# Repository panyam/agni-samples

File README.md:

# agni-samples

Real, publicly-licensed electronic designs that [agni](https://github.com/panyam/agni) reads in its
tests, its tutorial, and its reader cross-checks.

None of these designs are ours.  Someone else published each one under an open licence.  Each
folder keeps the upstream `LICENSE` that came with the design, and the KiCad boards under `boards/`
keep their upstream `README.md` too.  `PROVENANCE.md` records where each design came from, and what
was changed, if anything.

They live in their own repo, so the engine repo keeps a single licence and these keep theirs.

## The boards

| board | components | sheets | licence |
|---|---:|---:|---|
| `jetson-agx-thor-baseboard` | 1123 | 17 | Apache-2.0 |
| `royalblue54L-feather` | 71 | 1 | CERN-OHL-P |
| `hackrf-one` | 418 | 4 | CERN-OHL-P |
| `glasgow-revC3` | 257 | 3 | 0BSD |
| `cynthion` | 348 | 17 | CERN-OHL-P |
| `mnt-reform-motherboard30` | 529 | 13 | CERN-OHL-S |

ODB++ jobs sit apart, under `odb/` (see `PROVENANCE.md`).  Altium Designer wrote foxBMS's five
boards (CC-BY-4.0).  Allegro's tools wrote three more boards (CERN-OHL-S, CC-BY-4.0, OCP permissive).
kicad-cli exported each KiCad board above.

`cadence/` holds Cadence's other exports, and each has a `design.yaml`.  Allegro wrote the Parallella
parasdr to IPC-2581 and ODB++X (CC BY-SA 3.0 US), and its Allegro 16.6 board sits beside them.
OrCAD Capture wrote Clay R6 to EDIF (MIT).  Clay R6's Allegro 16.6 board sits beside it with
`pstxnet.dat`, the netlist Capture handed Allegro for that board.

`allegro/` holds Allegro boards, each as its publisher released it.  Four come from BeagleBoard.org
(CC-BY-4.0).  The BeagleBone AI comes with an extract that Allegro wrote from it.  BeaglePlay,
BeagleV-Fire and BeagleBone AI-64 come with other files Allegro wrote beside each board, such as
Gerbers and drill files, or a placement report.  BeagleBoard's Allegro boards use three `.brd`
header families, and these four cover all three.  The other two `.brd` boards are pc069 and the
OpenCellular breakout.  Each publisher also released an ODB++ job of the same board, under
`odb/allegro/`.  SLUGS v2 (MIT, Allegro 16.0), Parallella-I (CC BY-SA 3.0 US, 16.4) and the
ADALM1000 (CC BY-SA 3.0, 16.5) come from earlier releases, each with the netlist, films or exports
its publisher released beside it.

`altium/` holds Altium boards as Altium saved them.  The five foxBMS boards are binary `.PcbDoc`
files.  Two OpenSpeechPlatform boards (BSD-2-Clause) come as a binary `.PcbDoc` and the ASCII
`.PcbDoc` Altium saved of the same board, with their Gerbers.

`revisions/` holds later revisions of a board above, so two real revisions of one design can be
compared.  Antmicro's Jetson baseboard revs 1.1.2 and 1.1.3 sit there beside rev 1.1.0 in `boards/`
(Apache-2.0).  Rev 1.1.3 was saved by KiCad 10.  It ships in its own `revisions` tarball, so the oracle corpus the engine fetches on
every CI run stays the same size.  `make diff A=mount://boards/jetson-agx-thor-baseboard
B=mount://revisions/jetson-agx-thor-baseboard-1.1.2` compares the two.

`remote/` holds boards this repo may not redistribute, because their repos state no licence.  Only
`remote/remote.pin` is committed.  It names each file by its URL at a fixed commit and its sha256.
`make remote` downloads them from their publishers into a cache in `~/.cache/agni/samples`, so each
is downloaded once per machine, and copies them into `remote/<board>/`.  Three BeagleBoard.org
boards come this way: the BeagleBoard-X15 (Allegro 16.6), and the BeagleBone rev C2 and BeagleBone
Black rev B4 (16.4).  `make remote-clean` lists cache files unused for 30 days, and deletes them only
when you answer y.

## Opening them in agni

`agni serve` can open a checkout as it stands.  `agni.yaml` at the root mounts `boards/`, `odb/`,
`cadence/`, `allegro/`, `altium/`, `remote/` and `house/`, so `agni check mount://boards/hackrf-one` works at the
root with no flags.
Run it from the root.  agni finds `agni.yaml` from a subfolder too, but then reads its paths against
the folder you're in.  You need agni v0.6.0 or later, the first release that reads OrCAD Capture
designs, which Clay R6 is read from.  CI reads every design with v0.6.0 and with the latest release,
v0.6.2.  agni opens the seven binary `.PcbDoc` boards and five of the eleven Allegro `.brd` boards,
counting the two under `cadence/`.  BeaglePlay (Allegro 17.4), BeagleV-Fire (17.5), pc069, SLUGS v2,
Parallella-I and the ADALM1000 were saved by releases agni does not read yet (agni issue 1355), and
agni does not read an ASCII `.PcbDoc` yet (agni issue 1393).

```bash
make remote       # fetch the remote/ boards first, if you want them in the viewer
make serve        # the viewer over every board, job, native board and house board, at http://127.0.0.1:8080/
make serve-wasm   # the same, with each design analysed in your browser
make site         # the whole set as static files in site/, the way agni's public demo is built
```

`AGNI` names the binary and defaults to the `agni` on your PATH.  A release binary carries the
viewer.  A dev build (`make agni` in an agni checkout) carries none, so name its `web/` too:
`make serve AGNI=../agni/bin/agni WEB_DIR=../agni/web`.  `make site` and `make serve-wasm` need the
wasm engine built there as well (`make ui wasm`).  `PORT` moves the server, and `MCP=1` also serves
agni's analysis to an agent at `/mcp`.

`serve-wasm` caps a design at serve's `--wasm-max-bytes` (128 MB).  A bigger one goes to the server
engine, and the page says so.  Jetson is about 92 MB, so every board here runs in the browser.

`make verify` checks that each board folder has a `design.yaml` and a `PROVENANCE.md` section, and
that no `project.yaml` sits over the boards.  It also checks that each folder under `allegro/`,
`odb/allegro/` and `cadence/` has a `LICENSE` and a `PROVENANCE.md` heading, and that each design
under `cadence/` has a `design.yaml`.  `make verify AGNI=agni` also reads every design, job and house
board, and fails on any that reads as no components.  `make test` checks those checks, and CI runs
both.

## Your own boards beside these

A team can clone this repo and run every analysis on its own boards, after seeing each one work on a
public board first.  `make tour` runs every target below on Glasgow.

Your boards go in their own mount, `house`.  It defaults to `house/` in the checkout, and
`HOUSE_DIR=<folder>` moves it.  A folder outside the checkout is safer, since this repo is public.
`house/README.md` walks through adding a board from the template, with a `project.yaml` for your
team's conventions, checklists and query sets.  `make setup` installs a pre-commit hook that refuses
a commit with a house board in it.

Each target runs one agni command over `DESIGN=mount://...`.  `DESIGN` defaults to Glasgow.

| target | runs |
|---|---|
| `make check` | every rule, as text, and the verdict report in `reports/<name>-check.html` |
| `make review CHECKLIST=...` | a checklist walk, and its report in `reports/`.  Defaults to `examples/checklist.yaml` |
| `make diff A=... B=...` | the structural diff of two revisions or two views.  `RENAME_APPROX=1` pairs renamed nets that also changed |
| `make query SET=...` | a query set.  Defaults to `examples/queries.yaml` |
| `make trace FROM=U1.51 TO=U14.3` | the series path between two pins |
| `make lexicon` | the vocabulary agni uses to read the design's names |
| `make pinmap` | a row for each pin in the design's `io_map`, in `reports/<name>-pins.csv` |
| `make intake` | the sanitized summary, with no net name in it |
| `make trial` | the `agni trial` report, with no name from the design in it |

`reports/` is gitignored.  Every report in it carries your net names and reference designators,
except the intake and trial reports.  `DESIGN` and the other variables in the table take a value
from the make command line only.  So if your shell exports `DESIGN` for another project's Makefile,
these targets don't see it.

## Using these from the engine

The engine fetches a **pinned release tarball**, verified by checksum, into a gitignored directory.
It does not use a git submodule, so an engine clone does not carry this repo.

Tarballs are built per purpose, so a job downloads only what it needs:

| tarball | contents |
|---|---|
| `tutorial-board` | the Jetson baseboard, schematics only |
| `oracle-corpus` | every board, schematics and board files |
| `odb-altium` | ODB++ jobs Altium Designer wrote (the foxBMS boards), byte-identical to their publisher's |
| `altium` | the same foxBMS boards as Altium saved them (`.PcbDoc`), each held to its ODB++ export in `odb-altium`, and two OpenSpeechPlatform boards saved both as binary and as ASCII `.PcbDoc` |
| `odb-kicad` | each board above exported to ODB++ by kicad-cli, for reading a board both ways |
| `allegro` | the BeagleBone AI's Allegro `.brd`, with the extract Allegro wrote from the same board |
| `cadence-exports` | ODB++ jobs Allegro's tools wrote (`odb/allegro/`), and the IPC-2581 and EDIF exports under `cadence/` |
| `remote-boards` | `remote/remote.pin` alone, from which the engine fetches the `remote/` boards from their publishers |
| `revisions` | later revisions of the boards above, both views each, for comparing two revisions.  Only a demo or a revision example fetches it |
| `allegro-boards` | nine more Allegro `.brd` boards: six with the Gerbers, drill files, netlists, placement reports and OrCAD schematics their publishers released beside them, and three whose export is in `cadence-exports` |

`make dist` builds them all and writes `SHA256SUMS`.  `make list` prints the lines to pin.  `make
verify-dist` checks a built set against its sums.

Released artifacts are the pinned ones.  Verify a download against the `SHA256SUMS` attached to the
release rather than against a local rebuild, since archive metadata varies between machines.

## Adding a board

1. **Check the licence, and stop if there is not one.**  A design shipped with no LICENSE file cannot
   be redistributed here whatever its origin.  Permissive and reciprocal open-hardware licences are
   fine (PROVENANCE.md, "Reciprocal licences").  NonCommercial terms are not.
2. Copy the design **verbatim**, including its `LICENSE` and `README.md`.  Some tests compare a read
   against the upstream tool's own output, and an edited file can't serve as that reference.
3. Drop editor state and renders (`.kicad_prl`, `.lck`, `img/`).  Keep symbol and footprint libraries,
   since resolving them is under test.
4. Add a section to `PROVENANCE.md`: upstream, source, licence, date taken, and any modification.
5. Add a `design.yaml` naming its entry and companions (agni's `agni propose <folder>` drafts one).
   The next `make serve` serves it.  Don't add a `project.yaml` above it.  agni fails to load a
   design that sits under a `project.yaml` without naming it in `extends`.
6. Run `make verify AGNI=agni`.
7. Add it to a tarball target in the `Makefile` if a test needs it.

## Licence

Each design carries its own licence, and that licence governs its design files.  The top-level
`LICENSE` (Apache-2.0) covers only what this repo adds around them.  That means the Makefile, the
scripts under `hack/`, the `examples/` and `house/` templates, the provenance records, and the
`design.yaml` descriptors and `params/` facts that agni adds to a design.

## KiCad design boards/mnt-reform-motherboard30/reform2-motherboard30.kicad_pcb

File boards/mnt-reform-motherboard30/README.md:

# MNT Reform

This is the main repository for the MNT Reform open source laptop.

For details, check out [Finishing Reform](https://mntre.com/media/reform_md/2020-01-18-finishing-reform.html) and related articles.

## Impressions

## License

Copyright 2018-2020 MNT Research GmbH.

The following licenses are used in the project, unless specified differently in a particular subfolder:

- Schematics, PCBs: [CERN-OHL-S v2](https://www.ohwr.org/project/cernohl/wikis/uploads/002d0b7d5066e6b3829168730237bddb/cern_ohl_s_v2.txt)
- Other documentation, artwork, photos and drawings that are not trademarks (see below): [CC-BY-SA 4.0](https://creativecommons.org/licenses/by-sa/4.0/legalcode)
- Software, firmware: Various. [GPL 3.0](https://www.gnu.org/licenses/gpl-3.0.en.html) if not specified otherwise in the file/subdirectory.

The "MNT" and "MNT REFORM" logos are trademarks of MNT Research GmbH. You may not use these in derived works. The reason for this is that we cannot be responsible for regulatory issues with derived boards and we cannot support them. If someone sees an MNT brand on a product, it has to be clear that it comes from MNT Research and not from a third party.

## Made With

* [KiCAD EDA](http://kicad-pcb.org/)
* [OpenSCAD](https://www.openscad.org/)
* [LUFA](http://www.fourwalledcubicle.com/LUFA.php)
* Autodesk Fusion (Case parts)

## MNT Reform Team

* **Lukas F. Hartmann (mntmn)** - *Schematics, PCB*
* **Ana Dantas** - *Industrial Design*
* **Greta Melnik** - *Quality & Assembly, Sleeve*

## Credits and Contributions

* [fully automated technologies](https://fully.automated.ee/) - *inrush limiter circuit*

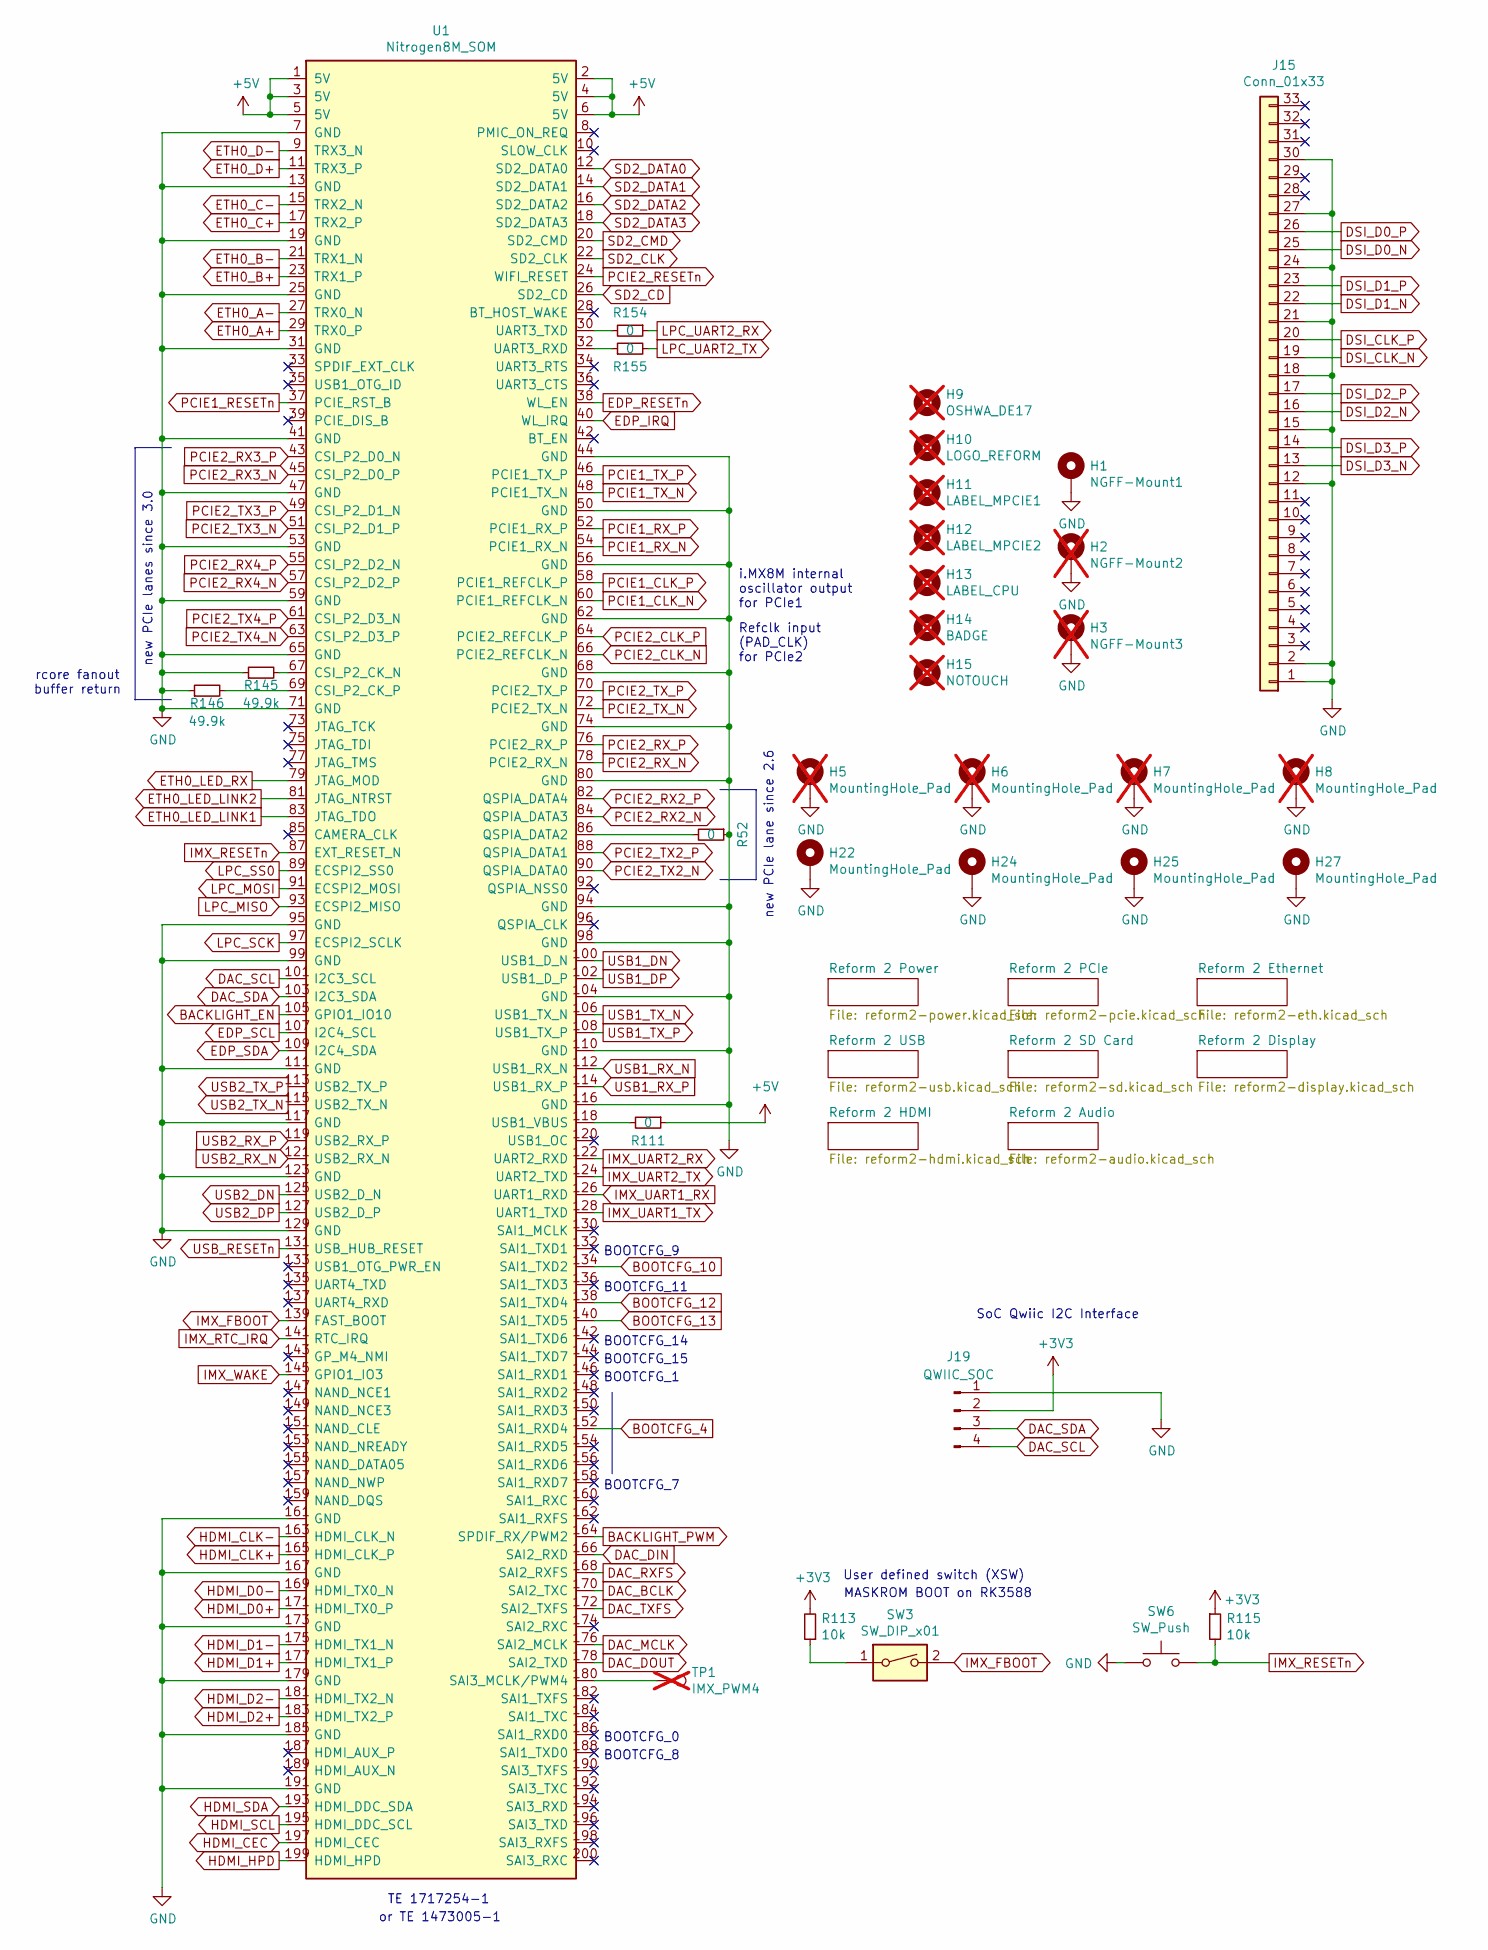
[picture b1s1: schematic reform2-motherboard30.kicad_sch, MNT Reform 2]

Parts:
H1: NGFF-Mount1; WA-SMSI-M2
H2: NGFF-Mount2; WA-SMSI-M2; not fitted
H3: NGFF-Mount3; WA-SMSI-M2; not fitted
H5, H6, H7, H8: MountingHole_Pad; MountingHole_2.2mm_M2_DIN965_Pad; not fitted
H9: OSHWA_DE17; oshwa-de17; not fitted
H10: LOGO_REFORM; mntreform; not fitted
H11: LABEL_MPCIE1; mpcie; not fitted
H12: LABEL_MPCIE2; nvme; not fitted
H13: LABEL_CPU; cpu; not fitted
H14: BADGE; reform2-motherboard-badge; not fitted
H15: NOTOUCH; ESD-Logo_8.9x8mm_SilkScreen; not fitted
H22, H24, H25, H27: MountingHole_Pad; WA-SMSI-M2
J15: Conn_01x33; Hirose_FH12-33S-0.5SH_1x33-1MP_P0.50mm_Horizontal
J19: QWIIC_SOC; JST_SH_SM04B-SRSS-TB_1x04-1MP_P1.00mm_Horizontal
R52, R111, R154, R155: 0; R_0603_1608Metric
R113, R115: 10k; R_0603_1608Metric
R145, R146: 49.9k; R_0603_1608Metric
SW3: SW_DIP_x01; SW_DIP_SPSTx01_Slide_Omron_A6S-110x_W8.9mm_P2.54mm
SW6: SW_Push; UK-B0206-G3.8-250-JZ
TP1: IMX_PWM4; TestPoint_Pad_D1.0mm; not fitted
U1: Nitrogen8M_SOM; TE_1473149-4

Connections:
+3V3: J19.2, R113.2, R115.1; also elsewhere on the board
+5V: R111.1, U1.1 (5V), U1.2 (5V), U1.3 (5V), U1.4 (5V), U1.5 (5V), U1.6 (5V); also elsewhere on the board
BACKLIGHT_EN: U1.105 (GPIO1_IO10); also elsewhere on the board
BACKLIGHT_PWM: U1.164 (SPDIF_RX/PWM2); also elsewhere on the board
BOOTCFG_4: U1.152 (SAI1_RXD4)
BOOTCFG_10: U1.134 (SAI1_TXD2)
BOOTCFG_12: U1.138 (SAI1_TXD4)
BOOTCFG_13: U1.140 (SAI1_TXD5)
DAC_BCLK: U1.170 (SAI2_TXC); also elsewhere on the board
DAC_DIN: U1.166 (SAI2_RXD); also elsewhere on the board
DAC_DOUT: U1.178 (SAI2_TXD); also elsewhere on the board
DAC_MCLK: U1.176 (SAI2_MCLK); also elsewhere on the board
DAC_RXFS: U1.168 (SAI2_RXFS); also elsewhere on the board
DAC_SCL: J19.4, U1.101 (I2C3_SCL); also elsewhere on the board
DAC_SDA: J19.3, U1.103 (I2C3_SDA); also elsewhere on the board
DAC_TXFS: U1.172 (SAI2_TXFS); also elsewhere on the board
DSI_CLK_N: J15.19; also elsewhere on the board
DSI_CLK_P: J15.20; also elsewhere on the board
DSI_D0_N: J15.25; also elsewhere on the board
DSI_D0_P: J15.26; also elsewhere on the board
DSI_D1_N: J15.22; also elsewhere on the board
DSI_D1_P: J15.23; also elsewhere on the board
DSI_D2_N: J15.16; also elsewhere on the board
DSI_D2_P: J15.17; also elsewhere on the board
DSI_D3_N: J15.13; also elsewhere on the board
DSI_D3_P: J15.14; also elsewhere on the board
EDP_IRQ: U1.40 (WL_IRQ); also elsewhere on the board
EDP_RESETn: U1.38 (WL_EN); also elsewhere on the board
EDP_SCL: U1.107 (I2C4_SCL); also elsewhere on the board
EDP_SDA: U1.109 (I2C4_SDA); also elsewhere on the board
ETH0_A+: U1.29 (TRX0_P); also elsewhere on the board
ETH0_A-: U1.27 (TRX0_N); also elsewhere on the board
ETH0_B+: U1.23 (TRX1_P); also elsewhere on the board
ETH0_B-: U1.21 (TRX1_N); also elsewhere on the board
ETH0_C+: U1.17 (TRX2_P); also elsewhere on the board
ETH0_C-: U1.15 (TRX2_N); also elsewhere on the board
ETH0_D+: U1.11 (TRX3_P); also elsewhere on the board
ETH0_D-: U1.9 (TRX3_N); also elsewhere on the board
ETH0_LED_LINK1: U1.83 (JTAG_TDO); also elsewhere on the board
ETH0_LED_LINK2: U1.81 (JTAG_NTRST); also elsewhere on the board
ETH0_LED_RX: U1.79 (JTAG_MOD); also elsewhere on the board
GND: H1.1, H2.1, H3.1, H5.1, H6.1, H7.1, H8.1, H22.1, H24.1, H25.1, H27.1, J15.1, J15.2, J15.12, J15.15, J15.18, J15.21, J15.24, J15.27, J15.30, J19.1, R52.1, R145.1, R146.1, SW6.1, U1.7 (GND), U1.13 (GND), U1.19 (GND), U1.25 (GND), U1.31 (GND), U1.41 (GND), U1.44 (GND), U1.47 (GND), U1.50 (GND), U1.53 (GND), U1.56 (GND), U1.59 (GND), U1.62 (GND), U1.65 (GND), U1.68 (GND), U1.71 (GND), U1.74 (GND), U1.80 (GND), U1.94 (GND), U1.95 (GND), U1.98 (GND), U1.99 (GND), U1.104 (GND), U1.110 (GND), U1.111 (GND), U1.116 (GND), U1.117 (GND), U1.123 (GND), U1.129 (GND), U1.161 (GND), U1.167 (GND), U1.173 (GND), U1.179 (GND), U1.185 (GND), U1.191 (GND); also elsewhere on the board
HDMI_CEC: U1.197 (HDMI_CEC); also elsewhere on the board
HDMI_CLK+: U1.165 (HDMI_CLK_P); also elsewhere on the board
HDMI_CLK-: U1.163 (HDMI_CLK_N); also elsewhere on the board
HDMI_D0+: U1.171 (HDMI_TX0_P); also elsewhere on the board
HDMI_D0-: U1.169 (HDMI_TX0_N); also elsewhere on the board
HDMI_D1+: U1.177 (HDMI_TX1_P); also elsewhere on the board
HDMI_D1-: U1.175 (HDMI_TX1_N); also elsewhere on the board
HDMI_D2+: U1.183 (HDMI_TX2_P); also elsewhere on the board
HDMI_D2-: U1.181 (HDMI_TX2_N); also elsewhere on the board
HDMI_HPD: U1.199 (HDMI_HPD); also elsewhere on the board
HDMI_SCL: U1.195 (HDMI_DDC_SCL); also elsewhere on the board
HDMI_SDA: U1.193 (HDMI_DDC_SDA); also elsewhere on the board
IMX_FBOOT: SW3.2, U1.139 (FAST_BOOT)
IMX_RESETn: R115.2, SW6.2, U1.87 (EXT_RESET_N); also elsewhere on the board
IMX_RTC_IRQ: U1.141 (RTC_IRQ); also elsewhere on the board
IMX_UART1_RX: U1.126 (UART1_RXD); also elsewhere on the board
IMX_UART1_TX: U1.128 (UART1_TXD); also elsewhere on the board
IMX_UART2_RX: U1.122 (UART2_RXD); also elsewhere on the board
IMX_UART2_TX: U1.124 (UART2_TXD); also elsewhere on the board
IMX_WAKE: U1.145 (GPIO1_IO3); also elsewhere on the board
LPC_MISO: U1.93 (ECSPI2_MISO); also elsewhere on the board
LPC_MOSI: U1.91 (ECSPI2_MOSI); also elsewhere on the board
LPC_SCK: U1.97 (ECSPI2_SCLK); also elsewhere on the board
LPC_SS0: U1.89 (ECSPI2_SS0); also elsewhere on the board
LPC_UART2_RX: R154.1; also elsewhere on the board
LPC_UART2_TX: R155.2; also elsewhere on the board
unnamed: R113.1, SW3.1
unnamed: R145.2, U1.67 (CSI_P2_CK_N)
unnamed: R146.2, U1.69 (CSI_P2_CK_P)
unnamed: R52.2, U1.86 (QSPIA_DATA2)
unnamed: TP1.1, U1.180 (SAI3_MCLK/PWM4)
unnamed: R155.1, U1.32 (UART3_RXD)
unnamed: R154.2, U1.30 (UART3_TXD)
unnamed: R111.2, U1.118 (USB1_VBUS)
PCIE1_CLK_N: U1.60 (PCIE1_REFCLK_N); also elsewhere on the board
PCIE1_CLK_P: U1.58 (PCIE1_REFCLK_P); also elsewhere on the board
PCIE1_RESETn: U1.37 (PCIE_RST_B); also elsewhere on the board
PCIE1_RX_N: U1.54 (PCIE1_RX_N); also elsewhere on the board
PCIE1_RX_P: U1.52 (PCIE1_RX_P); also elsewhere on the board
PCIE1_TX_N: U1.48 (PCIE1_TX_N); also elsewhere on the board
PCIE1_TX_P: U1.46 (PCIE1_TX_P); also elsewhere on the board
PCIE2_CLK_N: U1.66 (PCIE2_REFCLK_N); also elsewhere on the board
PCIE2_CLK_P: U1.64 (PCIE2_REFCLK_P); also elsewhere on the board
PCIE2_RESETn: U1.24 (WIFI_RESET); also elsewhere on the board
PCIE2_RX2_N: U1.84 (QSPIA_DATA3); also elsewhere on the board
PCIE2_RX2_P: U1.82 (QSPIA_DATA4); also elsewhere on the board
PCIE2_RX3_N: U1.45 (CSI_P2_D0_P); also elsewhere on the board
PCIE2_RX3_P: U1.43 (CSI_P2_D0_N); also elsewhere on the board
PCIE2_RX4_N: U1.57 (CSI_P2_D2_P); also elsewhere on the board
PCIE2_RX4_P: U1.55 (CSI_P2_D2_N); also elsewhere on the board
PCIE2_RX_N: U1.78 (PCIE2_RX_N); also elsewhere on the board
PCIE2_RX_P: U1.76 (PCIE2_RX_P); also elsewhere on the board
PCIE2_TX2_N: U1.90 (QSPIA_DATA0); also elsewhere on the board
PCIE2_TX2_P: U1.88 (QSPIA_DATA1); also elsewhere on the board
PCIE2_TX3_N: U1.51 (CSI_P2_D1_P); also elsewhere on the board
PCIE2_TX3_P: U1.49 (CSI_P2_D1_N); also elsewhere on the board
PCIE2_TX4_N: U1.63 (CSI_P2_D3_P); also elsewhere on the board
PCIE2_TX4_P: U1.61 (CSI_P2_D3_N); also elsewhere on the board
PCIE2_TX_N: U1.72 (PCIE2_TX_N); also elsewhere on the board
PCIE2_TX_P: U1.70 (PCIE2_TX_P); also elsewhere on the board
SD2_CD: U1.26 (SD2_CD); also elsewhere on the board
SD2_CLK: U1.22 (SD2_CLK); also elsewhere on the board
SD2_CMD: U1.20 (SD2_CMD); also elsewhere on the board
SD2_DATA0: U1.12 (SD2_DATA0); also elsewhere on the board
SD2_DATA1: U1.14 (SD2_DATA1); also elsewhere on the board
SD2_DATA2: U1.16 (SD2_DATA2); also elsewhere on the board
SD2_DATA3: U1.18 (SD2_DATA3); also elsewhere on the board
USB1_DN: U1.100 (USB1_D_N); also elsewhere on the board
USB1_DP: U1.102 (USB1_D_P); also elsewhere on the board
USB1_RX_N: U1.112 (USB1_RX_N); also elsewhere on the board
USB1_RX_P: U1.114 (USB1_RX_P); also elsewhere on the board
USB1_TX_N: U1.106 (USB1_TX_N); also elsewhere on the board
USB1_TX_P: U1.108 (USB1_TX_P); also elsewhere on the board
USB2_DN: U1.125 (USB2_D_N); also elsewhere on the board
USB2_DP: U1.127 (USB2_D_P); also elsewhere on the board
USB2_RX_N: U1.121 (USB2_RX_N); also elsewhere on the board
USB2_RX_P: U1.119 (USB2_RX_P); also elsewhere on the board
USB2_TX_N: U1.115 (USB2_TX_N); also elsewhere on the board
USB2_TX_P: U1.113 (USB2_TX_P); also elsewhere on the board
USB_RESETn: U1.131 (USB_HUB_RESET); also elsewhere on the board

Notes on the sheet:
rcore fanout buffer return
SoC Qwiic I2C Interface
BOOTCFG_7
BOOTCFG_0
TE 1717254-1
BOOTCFG_9
User defined switch (XSW)
BOOTCFG_14
BOOTCFG_15
new PCIe lanes since 3.0
BOOTCFG_1
BOOTCFG_11
MASKROM BOOT on RK3588
BOOTCFG_8
new PCIe lane since 2.6
i.MX8M internal oscillator output for PCIe1
Refclk input (PAD_CLK) for PCIe2
or TE 1473005-1

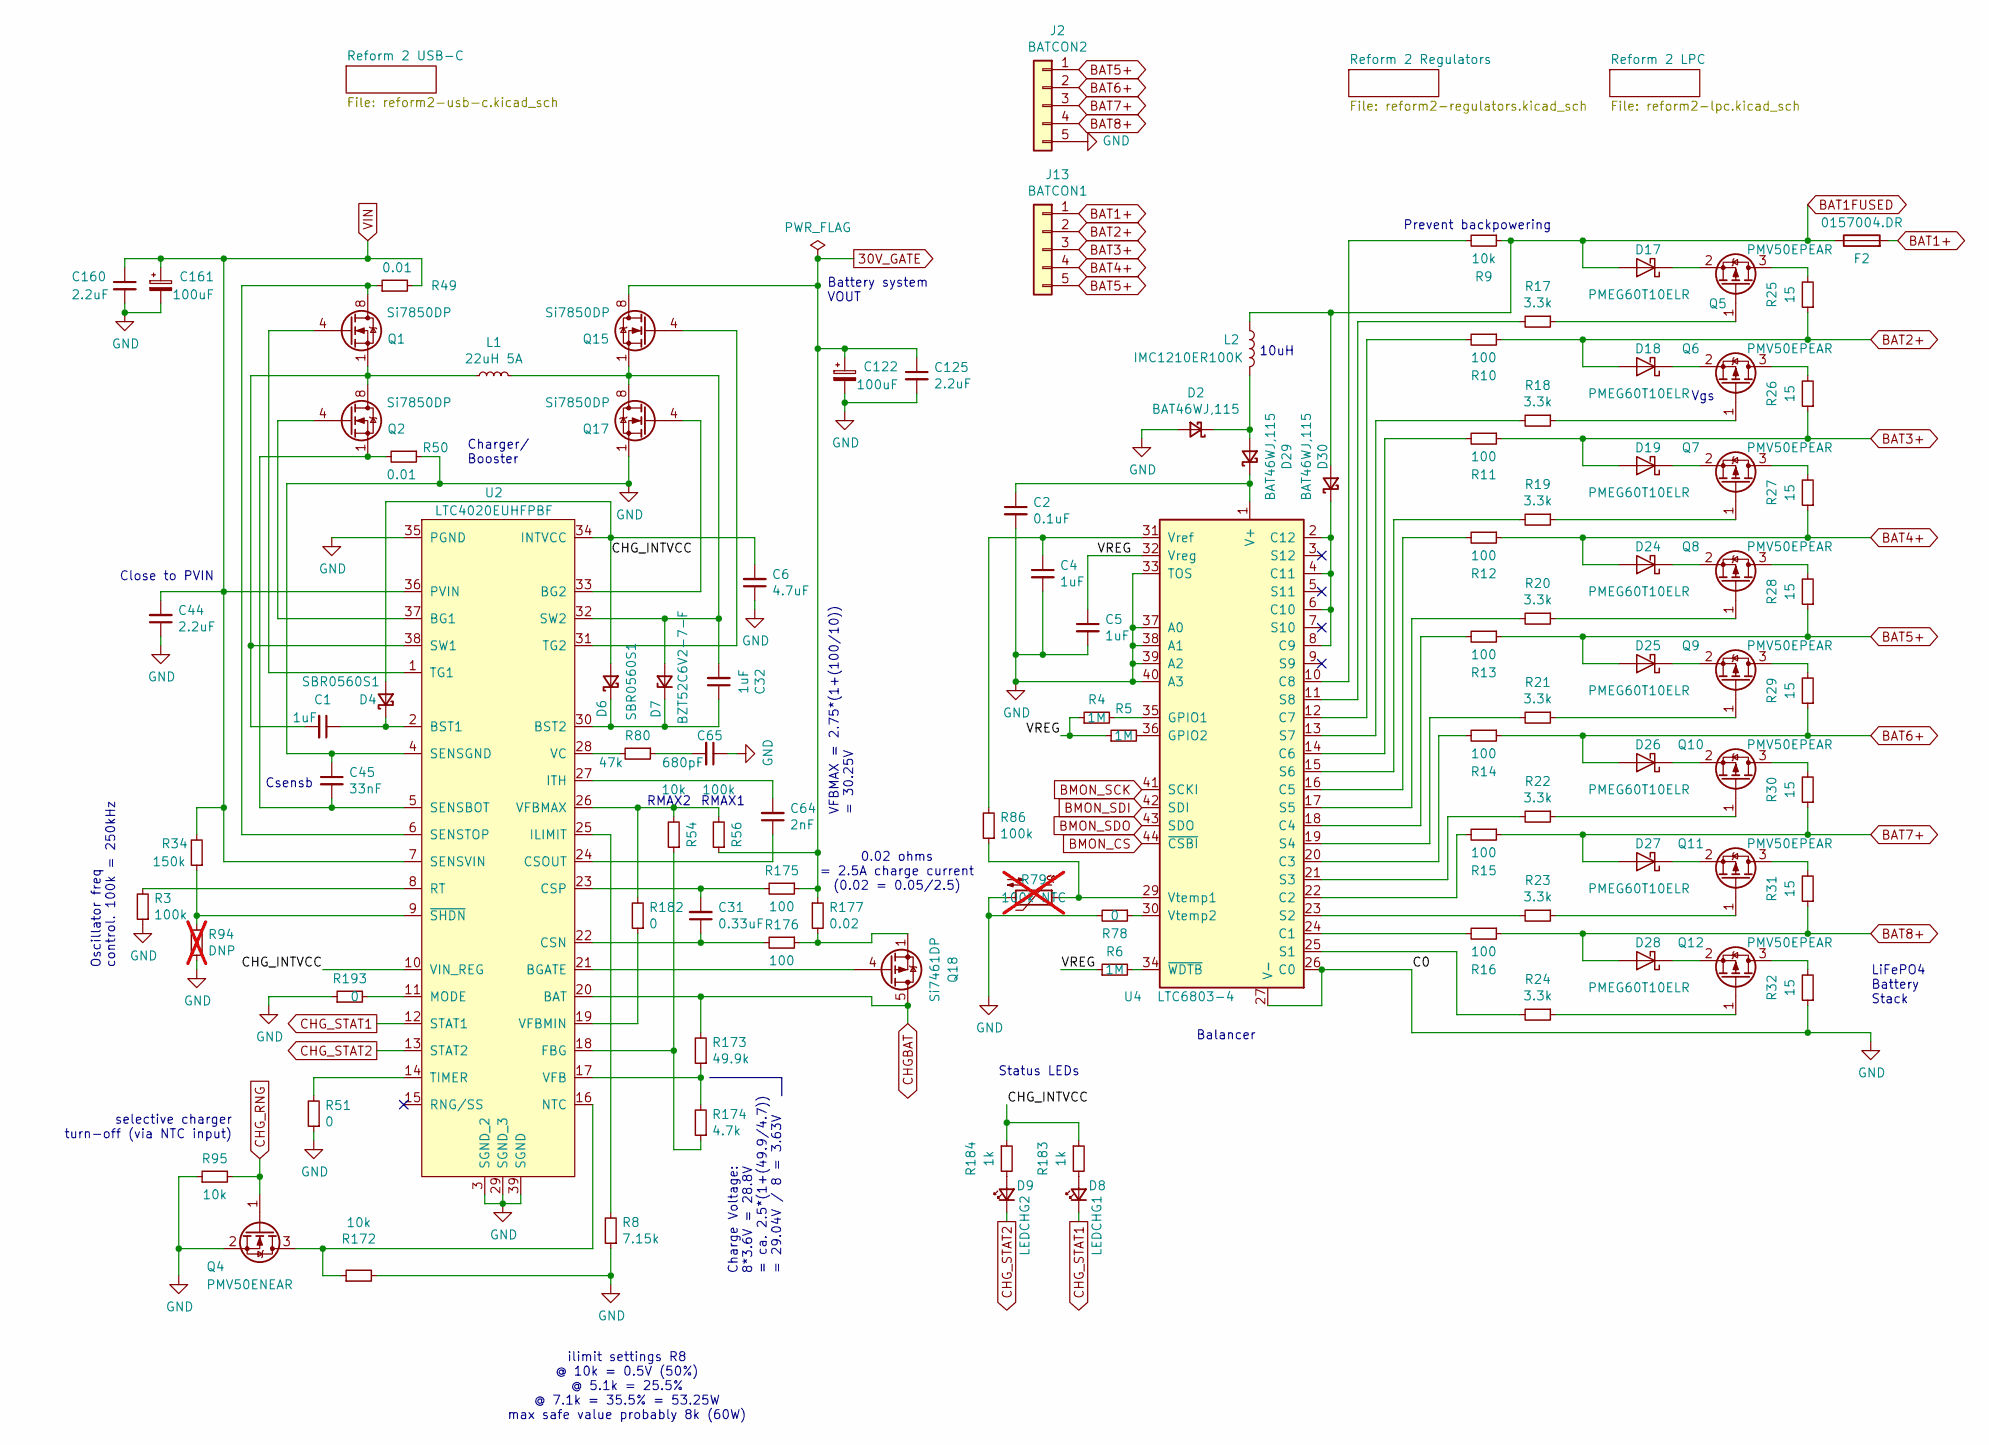
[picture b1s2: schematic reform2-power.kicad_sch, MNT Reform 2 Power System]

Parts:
C1, C4, C5, C32: 1uF; C_0603_1608Metric
C2: 0.1uF; C_0603_1608Metric
C6: 4.7uF; C_0603_1608Metric
C31: 0.33uF; C_0603_1608Metric
C44, C125, C160: 2.2uF; C_0603_1608Metric
C45: 33nF; C_0603_1608Metric
C64: 2nF; C_0603_1608Metric
C65: 680pF; C_0603_1608Metric
C122, C161: 100uF; CP_Elec_6.3x7.7
D2, D29, D30: BAT46WJ,115; D_SOD-323
D4, D6: SBR0560S1; D_SOD-123
D7: BZT52C6V2-7-F; D_SOD-123
D8: LEDCHG1; LED_0603_1608Metric
D9: LEDCHG2; LED_0603_1608Metric
D17, D18, D19, D24, D25, D26, D27, D28: PMEG60T10ELR; Nexperia_CFP3_SOD-123W
F2: 0157004.DR; fuse_smf
J2: BATCON2; Molex_Pico-Lock_504050-0591_1x05-1MP_P1.50mm_Horizontal
J13: BATCON1; Molex_Pico-Lock_504050-0591_1x05-1MP_P1.50mm_Horizontal
L1: 22uH 5A; L_12x12mm_H6mm
L2: IMC1210ER100K; L_1210_3225Metric
Q1, Q2, Q15, Q17: Si7850DP; PowerPAK_SO-8_Single_8Pads
Q4: PMV50ENEAR; SOT-23
Q5, Q6, Q7, Q8, Q9, Q10, Q11, Q12: PMV50EPEAR; SOT-23
Q18: Si7461DP; PowerPAK_SO-8_Single_8Pads
R3, R56, R86: 100k; R_0603_1608Metric
R4, R5, R6: 1M; R_0603_1608Metric
R8: 7.15k; R_0603_1608Metric
R9, R54, R95, R172: 10k; R_0603_1608Metric
R10, R11, R12, R13, R14, R15, R16, R175, R176: 100; R_0603_1608Metric
R17, R18, R19, R20, R21, R22, R23, R24: 3.3k; R_0603_1608Metric
R25, R26, R27, R28, R29, R30, R31, R32: 15; R_2512_6332Metric
R34: 150k; R_0603_1608Metric
R49, R50: 0.01; R_0612_1632Metric
R51, R78, R182, R193: 0; R_0603_1608Metric
R79: 100k NTC; R_0603_1608Metric; not fitted
R80: 47k; R_0603_1608Metric
R94: DNP; R_0603_1608Metric; not fitted
R173: 49.9k; R_0603_1608Metric
R174: 4.7k; R_0603_1608Metric
R177: 0.02; R_0612_1632Metric
R183, R184: 1k; R_0603_1608Metric
U2: LTC4020EUHFPBF; QFN-38-1EP_5x7mm_P0.5mm_EP3.15x5.15mm
U4: LTC6803-4; SSOP-44_5.3x12.8mm_P0.5mm

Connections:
30V_GATE: C122.1, C125.1, Q15.5 (D), Q15.6 (D), Q15.7 (D), Q15.8 (D), R56.1, R175.1, R177.1; also elsewhere on the board
/Reform 2 Power/CHG_INTVCC: C6.2, D4.2 (A), D6.2 (A), R183.1, R184.1, U2.10 (VIN_REG), U2.34 (INTVCC)
/Reform 2 Power/VREG: C5.1, R4.1, R5.1, R6.1, U4.32 (Vreg)
BAT1+: F2.2, J13.1
BAT1FUSED: D17.2 (A), D30.2 (A), F2.1, L2.1, R9.1; also elsewhere on the board
BAT2+: D18.2 (A), J13.2, R10.1, R25.1
BAT3+: D19.2 (A), J13.3, R11.1, R26.1
BAT4+: D24.2 (A), J13.4, R12.1, R27.1
BAT5+: D25.2 (A), J2.1, J13.5, R13.1, R28.1
BAT6+: D26.2 (A), J2.2, R14.1, R29.1
BAT7+: D27.2 (A), J2.3, R15.1, R30.1
BAT8+: D28.2 (A), J2.4, R16.1, R31.1
BMON_CS: U4.44 (~CSBI); also elsewhere on the board
BMON_SCK: U4.41 (SCKI); also elsewhere on the board
BMON_SDI: U4.42 (SDI); also elsewhere on the board
BMON_SDO: U4.43 (SDO); also elsewhere on the board
CHGBAT: Q18.5 (D), Q18.6 (D), Q18.7 (D), Q18.8 (D), R173.2, U2.20 (BAT); also elsewhere on the board
CHG_RNG: Q4.1 (G), R95.2; also elsewhere on the board
CHG_STAT1: D8.1 (K), U2.12 (STAT1)
CHG_STAT2: D9.1 (K), U2.13 (STAT2)
GND: C2.2, C4.2, C5.2, C6.1, C44.1, C45.1, C65.1, C122.2, C125.2, C160.2, C161.2, D2.2 (A), J2.5, Q4.2 (S), Q17.1 (S), Q17.2 (S), Q17.3 (S), R3.1, R8.1, R32.1, R50.1, R51.1, R78.2, R79.2, R94.1, R95.1, R172.2, R193.1, U2.3 (SGND_2), U2.4 (SENSGND), U2.29 (SGND_3), U2.35 (PGND), U2.39 (SGND), U4.26 (C0), U4.27 (V-), U4.33 (TOS), U4.37 (A0), U4.38 (A1), U4.39 (A2), U4.40 (A3); also elsewhere on the board
unnamed: C65.2, R80.1
unnamed: D2.1 (K), D29.2 (A), L2.2
unnamed: C1.1, D4.1 (K), U2.2 (BST1)
unnamed: C32.1, D6.1 (K), D7.1 (K), U2.30 (BST2)
unnamed: C32.2, D7.2 (A), L1.2, Q15.1 (S), Q15.2 (S), Q15.3 (S), Q17.5 (D), Q17.6 (D), Q17.7 (D), Q17.8 (D), U2.32 (SW2)
unnamed: D8.2 (A), R183.2
unnamed: D9.2 (A), R184.2
unnamed: D17.1 (K), Q5.2 (S)
unnamed: D18.1 (K), Q6.2 (S)
unnamed: D19.1 (K), Q7.2 (S)
unnamed: D24.1 (K), Q8.2 (S)
unnamed: D25.1 (K), Q9.2 (S)
unnamed: D26.1 (K), Q10.2 (S)
unnamed: D27.1 (K), Q11.2 (S)
unnamed: D28.1 (K), Q12.2 (S)
unnamed: C2.1, D29.1 (K), U4.1 (V+)
unnamed: D30.1 (K), U4.2 (C12), U4.4 (C11), U4.6 (C10), U4.8 (C9)
unnamed: Q1.4 (G), U2.1 (TG1)
unnamed: Q2.4 (G), U2.37 (BG1)
unnamed: Q4.3 (D), R172.1, U2.16 (NTC)
unnamed: Q5.3 (D), R25.2
unnamed: Q5.1 (G), R17.1
unnamed: Q6.3 (D), R26.2
unnamed: Q6.1 (G), R18.1
unnamed: Q7.3 (D), R27.2
unnamed: Q7.1 (G), R19.1
unnamed: Q8.3 (D), R28.2
unnamed: Q8.1 (G), R20.1
unnamed: Q9.3 (D), R29.2
unnamed: Q9.1 (G), R21.1
unnamed: Q10.3 (D), R30.2
unnamed: Q10.1 (G), R22.1
unnamed: Q11.3 (D), R31.2
unnamed: Q11.1 (G), R23.1
unnamed: Q12.3 (D), R32.2
unnamed: Q12.1 (G), R24.1
unnamed: Q15.4 (G), U2.31 (TG2)
unnamed: Q17.4 (G), U2.33 (BG2)
unnamed: Q18.4 (G), U2.21 (BGATE)
unnamed: Q18.1 (S), Q18.2 (S), Q18.3 (S), R176.1, R177.2
unnamed: C31.1, R176.2, U2.22 (CSN)
unnamed: C64.1, U2.24 (CSOUT)
unnamed: C31.2, R175.2, U2.23 (CSP)
unnamed: R54.1, R174.1, U2.18 (FBG)
unnamed: R8.2, U2.25 (ILIMIT)
unnamed: C64.2, U2.27 (ITH)
unnamed: R193.2, U2.11 (MODE)
unnamed: R3.2, U2.8 (RT)
unnamed: C45.2, Q2.1 (S), Q2.2 (S), Q2.3 (S), R50.2, U2.5 (SENSBOT)
unnamed: Q1.5 (D), Q1.6 (D), Q1.7 (D), Q1.8 (D), R49.1, U2.6 (SENSTOP)
unnamed: C1.2, L1.1, Q1.1 (S), Q1.2 (S), Q1.3 (S), Q2.5 (D), Q2.6 (D), Q2.7 (D), Q2.8 (D), U2.38 (SW1)
unnamed: R51.2, U2.14 (TIMER)
unnamed: R80.2, U2.28 (VC)
unnamed: R173.1, R174.2, U2.17 (VFB)
unnamed: R54.2, R56.2, R182.2, U2.26 (VFBMAX)
unnamed: R182.1, U2.19 (VFBMIN)
unnamed: R34.1, R94.2, U2.9 (~SHDN)
unnamed: R16.2, U4.24 (C1)
unnamed: R15.2, U4.22 (C2)
unnamed: R14.2, U4.20 (C3)
unnamed: R13.2, U4.18 (C4)
unnamed: R12.2, U4.16 (C5)
unnamed: R11.2, U4.14 (C6)
unnamed: R10.2, U4.12 (C7)
unnamed: R9.2, U4.10 (C8)
unnamed: R4.2, U4.35 (GPIO1)
unnamed: R5.2, U4.36 (GPIO2)
unnamed: R24.2, U4.25 (S1)
unnamed: R23.2, U4.23 (S2)
unnamed: R22.2, U4.21 (S3)
unnamed: R21.2, U4.19 (S4)
unnamed: R20.2, U4.17 (S5)
unnamed: R19.2, U4.15 (S6)
unnamed: R18.2, U4.13 (S7)
unnamed: R17.2, U4.11 (S8)
unnamed: C4.1, R86.2, U4.31 (Vref)
unnamed: R79.1, R86.1, U4.29 (Vtemp1)
unnamed: R78.1, U4.30 (Vtemp2)
unnamed: R6.2, U4.34 (~WDTB)
VIN: C44.2, C160.1, C161.1, R34.2, R49.2, U2.7 (SENSVIN), U2.36 (PVIN); also elsewhere on the board

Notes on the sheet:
0.02 ohms = 2.5A charge current (0.02 = 0.05/2.5)
Vgs
Oscillator freq control. 100k = 250kHz
Csensb
Charge Voltage: 8*3.6V = 28.8V = ca. 2.5*(1+(49.9/4.7)) = 29.04V / 8 = 3.63V
Close to PVIN
10uH
LiFePO4 Battery Stack
Battery system VOUT
selective charger turn-off (via NTC input)
Status LEDs
VFBMAX = 2.75*(1+(100/10)) = 30.25V
RMAX2
Prevent backpowering
RMAX1
Balancer
Charger/ Booster
ilimit settings R8 @ 10k = 0.5V (50%) @ 5.1k = 25.5% @ 7.1k = 35.5% = 53.25W max safe value probably 8k (60W)

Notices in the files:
boards/mnt-reform-motherboard30/reform2-audio.kicad_sch:
License: CERN-OHL-S 2.0
